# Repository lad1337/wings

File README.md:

# Wings an ultra low profile split wireless keyboard

WIP Ultra low profile split keyboard using the kailh pg1316s.
[ergogen](https://github.com/ergogen/ergogen) was used to generate the position and overal shape.
My [fork](https://github.com/lad1337/ergogen) was used and it allows footprints to generate new net connections.
A special footprint *Placeholder* is used located at `config/footprints/placeholder.js`.
It also uses some [custom  footprints](https://github.com/lad1337/lad1337.pretty) i created

## Images

## Firmware

use [enki 42 zmk firmware with n!n dongle](https://github.com/aroum/zmk-enki42-dongle/tree/N!N_v2)

## Hardware

- 3 seeed xiao BLE (running in dongle mode)
- 60 kailh pg1316s
- 301230 3,7 V lipo (30 x 12 x 3)
- 1N4148W SOD-123 1206

## TODOS

- [x] Make it revsible
- [x] Route the board
- [x] Order keys and diods and hotplate
- [x] Santity check PCB
- [x] Order PCB
- [ ] Solder

## Other

- background wings art from https://pixabay.com/vectors/wing-angel-feathers-bird-white-295393/

## License

<p xmlns:cc="http://creativecommons.org/ns#" xmlns:dct="http://purl.org/dc/terms/"><a property="dct:title" rel="cc:attributionURL" href="https://github.com/lad1337/wings">wings</a> by <a rel="cc:attributionURL dct:creator" property="cc:attributionName" href="https://github.com/lad1337">lad1337</a> is licensed under <a href="https://creativecommons.org/licenses/by-nc-sa/4.0/?ref=chooser-v1" target="_blank" rel="license noopener noreferrer" style="display:inline-block;">CC BY-NC-SA 4.0</a></p>

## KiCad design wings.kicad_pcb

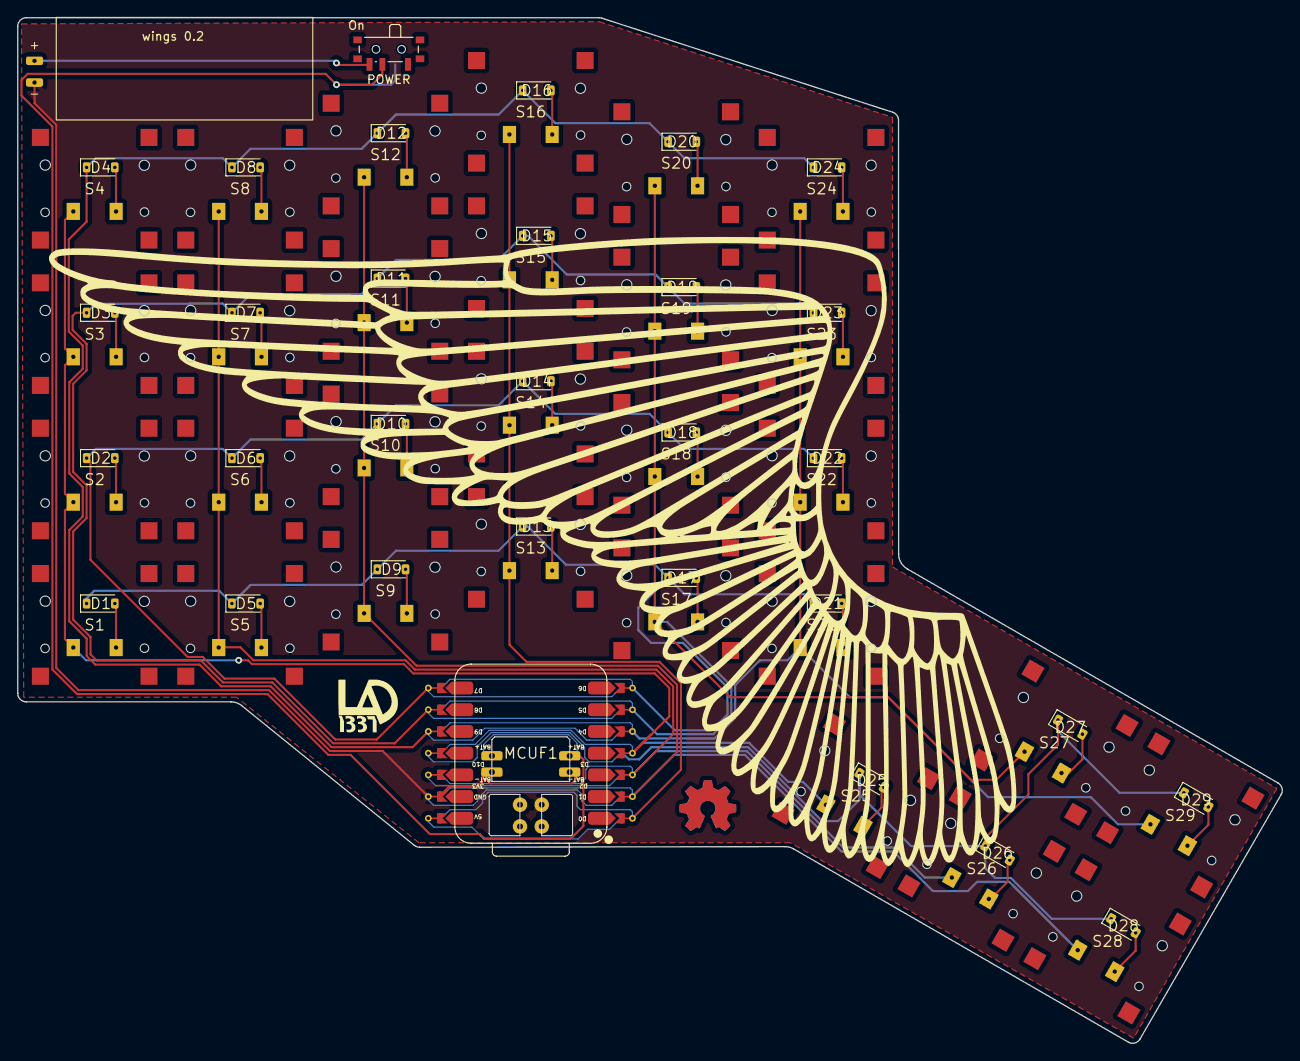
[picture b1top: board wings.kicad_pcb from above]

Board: 2 copper layers, 147.9 x 119.9 mm, 61 parts (0 on the bottom side), 43 nets.

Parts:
D1, D2, D3, D4, D5, D6, D7, D8, D9, D10, D11, D12, D13, D14, D15, D16, D17, D18, D19, D20, D21, D22, D23, D24, D25, D26, D27, D28, D29: D_SOD-123-reversible
MCUF1: XIAO-nRF52840-SMD-reversible
POWER: SW_SPDT_PCM12_reversible
S1, S2, S3, S4, S5, S6, S7, S8, S9, S10, S11, S12, S13, S14, S15, S16, S17, S18, S19, S20, S21, S22, S23, S24, S25, S26, S27, S28, S29: CPG1316S01D02_reversible
battery1: lipo-reversible

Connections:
BAT+: POWER.1, POWER.3, battery1.1
GND: MCUF1.13, MCUF1.16, MCUF1.19, battery1.2
P0: MCUF1.1, S13.1, S14.1, S15.1, S16.1
P1: MCUF1.2, S9.1, S10.1, S11.1, S12.1, S28.1
P2: MCUF1.3, S5.1, S6.1, S7.1, S8.1, S26.1
P3: MCUF1.4, S1.1, S2.1, S3.1, S4.1, S25.1
P4: MCUF1.5, S21.1, S22.1, S23.1, S24.1, S29.1
P5: MCUF1.6, S17.1, S18.1, S19.1, S20.1, S27.1
P6: D1.1, D5.1, D9.1, D13.1, D17.1, D21.1, MCUF1.7
P7: D2.1, D6.1, D10.1, D14.1, D18.1, D22.1, MCUF1.8
P8: D3.1, D7.1, D11.1, D15.1, D19.1, D23.1, MCUF1.9
P9: D4.1, D8.1, D12.1, D16.1, D20.1, D24.1, MCUF1.10
P10: D25.1, D26.1, D27.1, D28.1, D29.1, MCUF1.11
VIN: MCUF1.15, POWER.2
far_bottom: D28.2, S28.2
far_top: D29.2, S29.2
home_bottom: D26.2, S26.2
home_top: D27.2, S27.2
index_bottom: D17.2, S17.2
index_home: D18.2, S18.2
index_numbers: D20.2, S20.2
index_top: D19.2, S19.2
inner_bottom: D21.2, S21.2
inner_home: D22.2, S22.2
inner_numbers: D24.2, S24.2
inner_top: D23.2, S23.2
middle_bottom: D13.2, S13.2
middle_home: D14.2, S14.2
middle_numbers: D16.2, S16.2
middle_top: D15.2, S15.2
near_bottom: D25.2, S25.2
outer_bottom: D1.2, S1.2
outer_home: D2.2, S2.2
outer_numbers: D4.2, S4.2
outer_top: D3.2, S3.2
pinky_bottom: D5.2, S5.2
pinky_home: D6.2, S6.2
pinky_numbers: D8.2, S8.2
pinky_top: D7.2, S7.2
ring_bottom: D9.2, S9.2
ring_home: D10.2, S10.2
ring_numbers: D12.2, S12.2
ring_top: D11.2, S11.2

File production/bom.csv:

Designator,Footprint,Quantity,Value,LCSC Part #
BATTERY1,lipo-reversible,1,,
"D1, D10, D11, D12, D13, D14, D15, D16, D17, D18, D19, D2, D20, D21, D22, D23, D24, D25, D26, D27, D28, D29, D3, D4, D5, D6, D7, D8, D9",D_SOD-123-reversible,29,,
MCUF1,XIAO-nRF52840-SMD-reversible,1,,
POWER,SW_SPDT_PCM12_reversible,1,SW_SPDT_PCM12_reversible,
"S1, S10, S11, S12, S13, S14, S15, S16, S17, S18, S19, S2, S20, S21, S22, S23, S24, S25, S26, S27, S28, S29, S3, S4, S5, S6, S7, S8, S9",CPG1316S01D02_reversible,29,,

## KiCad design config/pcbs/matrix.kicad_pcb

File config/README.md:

# Wings ultra low profile wireless keyboard

## Firmware

use [enki 42 zmk firmware with n!n dongle](https://github.com/aroum/zmk-enki42-dongle/tree/N!N_v2)

## Hardware

- 3 seeed xiao BLE
- many kailh pg1316s
- 301230 3,7 V lipo (30 x 12 x 3)
- 1N4148W SOD-123 1206 SMD-Schaltdiode 1N4148 SOD123
- 

## Other
- background wings art from https://pixabay.com/vectors/wing-angel-feathers-bird-white-295393/

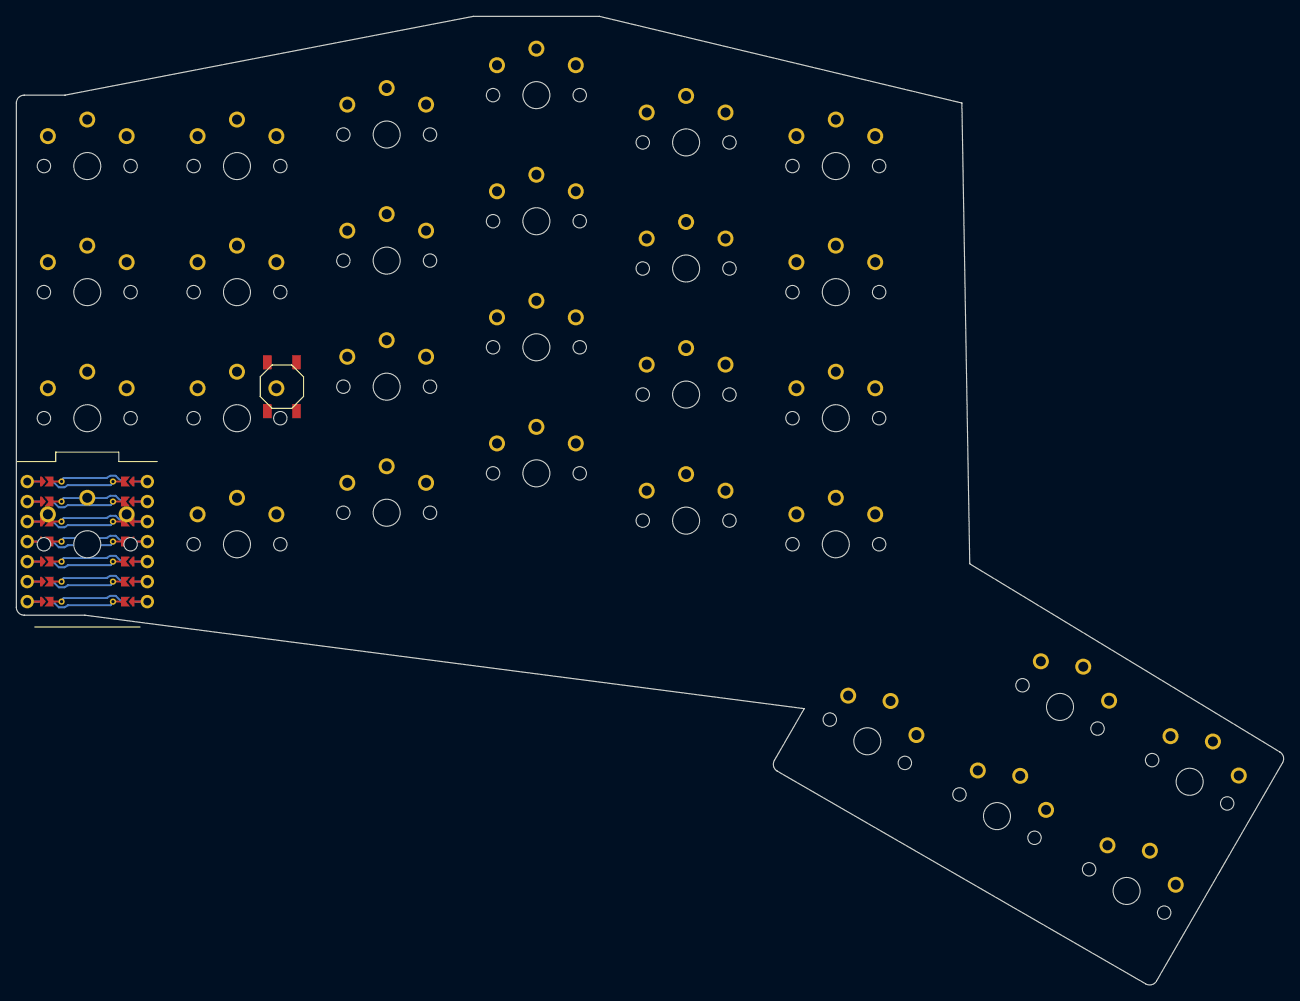
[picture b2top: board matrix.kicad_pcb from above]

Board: 2 copper layers, 160.8 x 122.9 mm, 32 parts (0 on the bottom side), 2 nets.

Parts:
B1, B2: SW_TACT_ALPS_SKQGABE010
MCU1: seeed_xiao
S1, S2, S3, S4, S5, S6, S7, S8, S9, S10, S11, S12, S13, S14, S15, S16, S17, S18, S19, S20, S21, S22, S23, S24, S25, S26, S27, S28, S29: PG1350

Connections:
GND: B1.2, B2.2, MCU1.123
RST: B1.1, B2.1

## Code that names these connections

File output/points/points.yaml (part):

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        autobind: 10
        skip: false
        asym: both
        colrow: pinky_bottom
        name: matrix_pinky_bottom
        col_net: P2
        row_net: P6
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        autobind: 10
        skip: false
        asym: both
        colrow: pinky_home
        name: matrix_pinky_home
        col_net: P2
        row_net: P7
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        autobind: 10
        skip: false
        asym: both
        colrow: pinky_top
        name: matrix_pinky_top
        col_net: P2
        row_net: P8
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        autobind: 10
        skip: false
        asym: both
        colrow: pinky_numbers
        name: matrix_pinky_numbers
        col_net: P2
        row_net: P9
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
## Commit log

2024-11-10 inital need more cleanup
2024-11-10 repo cleanup
2024-11-10 new production files
2024-11-10 add license
2024-11-11 add version markings and new production files
    this is the version send to production!
2024-11-14 ignore all autosaves
2024-11-25 updates xiao footprint
2024-11-25 mark steps
2024-11-25 fix: top thumbs were only a copy of bottom row
2024-11-27 add all ergogen outputs
2024-11-27 add zmk config
2024-11-27 FIX: the pads for battery -/+ where swapped -.-
2024-11-27 add makefile
2024-11-27 add firmware (untested)
2024-11-28 switch keys for thumbs for easier tracing
2024-11-28 new pcb with fill zone and fixed thumb
2024-11-28 no need to print the commands
2024-11-28 battery reporting and streamline config
